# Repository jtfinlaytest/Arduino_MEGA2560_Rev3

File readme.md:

# Sample Arduino board for Cadstrom webhook validations.

Touch8

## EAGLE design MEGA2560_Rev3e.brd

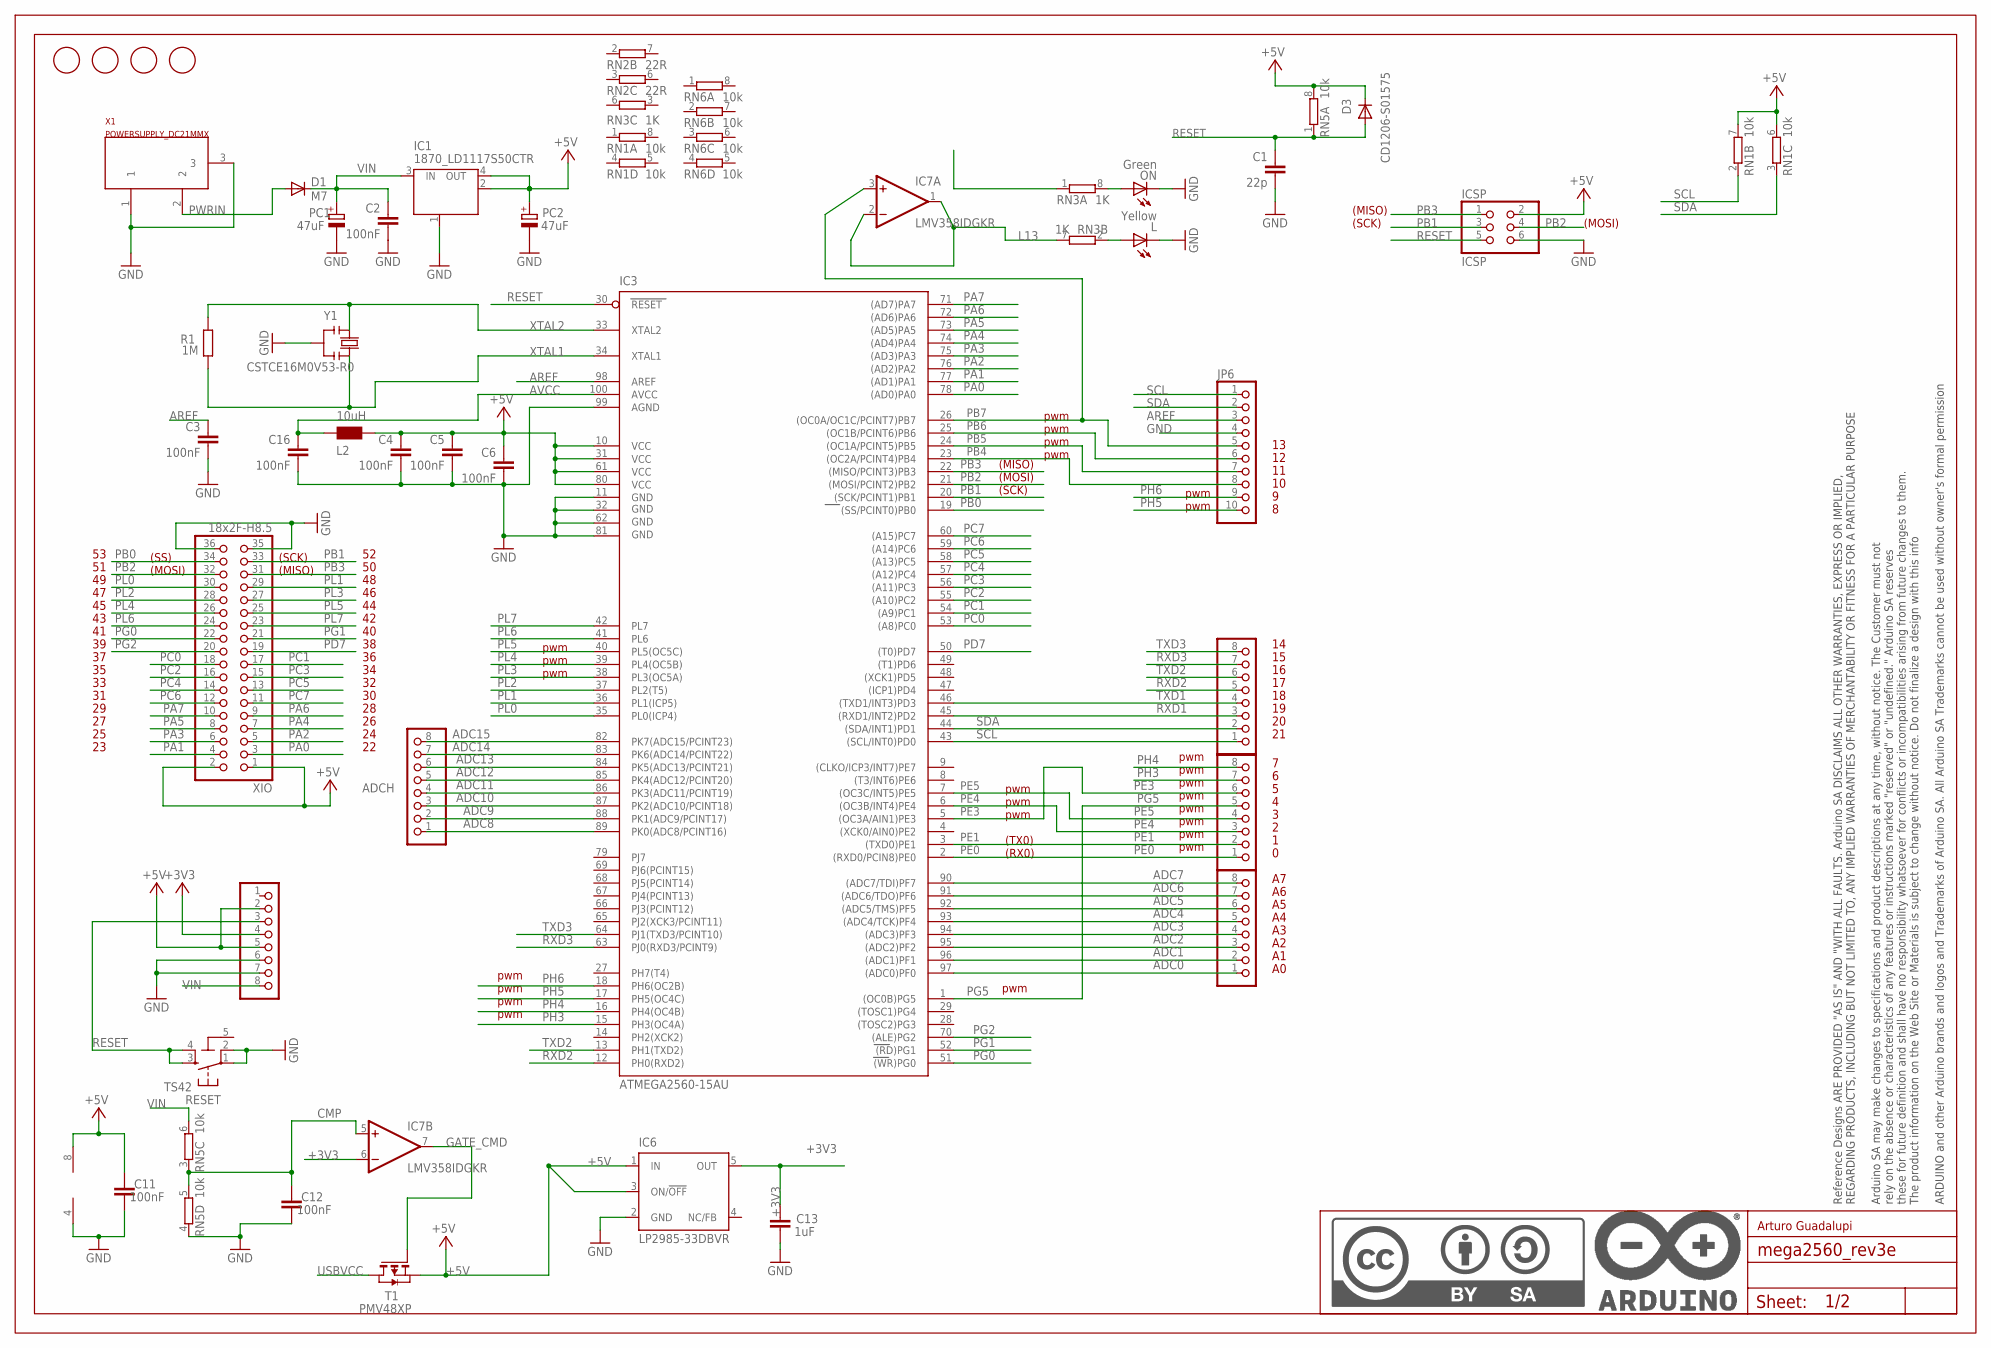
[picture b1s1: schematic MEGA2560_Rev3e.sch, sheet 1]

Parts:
ADCH: FH254-108DF08500V; 1X08
ADCL: FH254-108DF08500V; 1X08
C1: 22p; C0603-ROUND
C2, C3, C4, C5, C6, C11, C12, C16: 100nF; C0603-ROUND
C13: 1uF; C0603-ROUND
COMMUNICATION: FH254-108DF08500V; 1X08
D1: M7; SMB
D3: CD1206-S01575; MINIMELF
FD1, FD2, FD3, FD4: FIDUCIALMOUNT; FIDUCIA-MOUNT
IC1: 1870_LD1117S50CTR; LINEAR_SOT223
IC3: ATMEGA2560-15AU; TQFP100
IC6: LP2985-33DBVR; SOT23-DBV
IC7: LMV358IDGKR; MSOP08
ICSP: ICSP; 2X03
JP6: FH254-110DF08500V; 1X10
L: Yellow; CHIPLED_0805
L2: 10uH; 0805
ON: Green; CHIPLED_0805
PC1, PC2: 47uF; PANASONIC_D
POWER: FH254-108DF08500V; 1X08
PWML: FH254-108DF08500V; 1X08
R1: 1M; R0603-ROUND
RESET: TS42
RN1, RN5, RN6: 10k; CAY16
RN2: 22R; CAY16
RN3: 1K; CAY16
T1: PMV48XP; SOT-23; PART_NUMBER PMV48XP
U$1: DNP; FRAME
X1: POWERSUPPLY_DC21MMX; POWERSUPPLY_DC-21MM
XIO: 18x2F-H8.5; 2X18
Y1: CSTCE16M0V53-R0; RESONATOR

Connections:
5-GND: RESET.5 (5-GND)
+3V3: C13.2, IC6.5 (OUT), IC7.6 (-IN), POWER.4
+5V: C4.1, C5.1, C6.1, C11.2, D3.C, IC1.2 (OUT), IC1.4 (OUT), IC3.10 (VCC), IC3.31 (VCC1), IC3.61 (VCC2), IC3.80 (VCC3), IC6.1 (IN), IC6.3 (ON/!OFF), IC7.8 (V+), ICSP.2, L2.2, PC2.+, POWER.2, POWER.5, RN1.6 (2), RN1.7 (2), RN5.8 (2), T1.2 (S), XIO.1, XIO.2; also elsewhere on the board
ADC0: ADCL.1, IC3.97 ((ADC0)PF0)
ADC1: ADCL.2, IC3.96 ((ADC1)PF1)
ADC2: ADCL.3, IC3.95 ((ADC2)PF2)
ADC3: ADCL.4, IC3.94 ((ADC3)PF3)
ADC4: ADCL.5, IC3.93 ((ADC4/TCK)PF4)
ADC5: ADCL.6, IC3.92 ((ADC5/TMS)PF5)
ADC6: ADCL.7, IC3.91 ((ADC6/TDO)PF6)
ADC7: ADCL.8, IC3.90 ((ADC7/TDI)PF7)
ADC8: ADCH.1, IC3.89 (PK0(ADC8/PCINT16))
ADC9: ADCH.2, IC3.88 (PK1(ADC9/PCINT17))
ADC10: ADCH.3, IC3.87 (PK2(ADC10/PCINT18))
ADC11: ADCH.4, IC3.86 (PK3(ADC11/PCINT19))
ADC12: ADCH.5, IC3.85 (PK4(ADC12/PCINT20))
ADC13: ADCH.6, IC3.84 (PK5(ADC13/PCINT21))
ADC14: ADCH.7, IC3.83 (PK6(ADC14/PCINT22))
ADC15: ADCH.8, IC3.82 (PK7(ADC15/PCINT23))
AREF: C3.1, IC3.98 (AREF), JP6.3
AVCC: C16.1, IC3.100 (AVCC), L2.1
CMP: C12.2, IC7.5 (+IN), RN5.3 (1), RN5.5 (2)
GATE_CMD: IC7.7 (OUT), T1.3 (G)
GND: C1.2, C2.2, C3.2, C4.2, C5.2, C6.2, C11.1, C12.1, C13.1, C16.2, IC1.1 (GND/ADJ), IC3.11 (GND), IC3.32 (GND1), IC3.62 (GND2), IC3.81 (GND3), IC3.99 (AGND), IC6.2 (GND), IC7.4 (V-), ICSP.6, JP6.4, L.C, ON.C, PC1.-, PC2.-, POWER.6, POWER.7, RESET.1, RESET.2, RN5.4 (1), X1.1, X1.3, XIO.35, XIO.36, Y1.2; also elsewhere on the board
L13: IC7.1 (OUT), IC7.2 (-IN), RN3.7 (2)
unnamed: L.A, RN3.2 (1)
unnamed: ON.A, RN3.8 (2)
PA0: IC3.78 ((AD0)PA0), XIO.3
PA1: IC3.77 ((AD1)PA1), XIO.4
PA2: IC3.76 ((AD2)PA2), XIO.5
PA3: IC3.75 ((AD3)PA3), XIO.6
PA4: IC3.74 ((AD4)PA4), XIO.7
PA5: IC3.73 ((AD5)PA5), XIO.8
PA6: IC3.72 ((AD6)PA6), XIO.9
PA7: IC3.71 ((AD7)PA7), XIO.10
PB0: IC3.19 ((SS/PCINT0)PB0), XIO.34
PB1: IC3.20 ((SCK/PCINT1)PB1), ICSP.3, XIO.33
PB2: IC3.21 ((MOSI/PCINT2)PB2), ICSP.4, XIO.32
PB3: IC3.22 ((MISO/PCINT3)PB3), ICSP.1, XIO.31
PB4: IC3.23 ((OC2A/PCINT4)PB4), JP6.8
PB5: IC3.24 ((OC1A/PCINT5)PB5), JP6.7
PB6: IC3.25 ((OC1B/PCINT6)PB6), JP6.6
PB7: IC3.26 ((OC0A/OC1C/PCINT7)PB7), IC7.3 (+IN), JP6.5
PC0: IC3.53 ((A8)PC0), XIO.18
PC1: IC3.54 ((A9)PC1), XIO.17
PC2: IC3.55 ((A10)PC2), XIO.16
PC3: IC3.56 ((A11)PC3), XIO.15
PC4: IC3.57 ((A12)PC4), XIO.14
PC5: IC3.58 ((A13)PC5), XIO.13
PC6: IC3.59 ((A14)PC6), XIO.12
PC7: IC3.60 ((A15)PC7), XIO.11
PD7: IC3.50 ((T0)PD7), XIO.19
PE0: IC3.2 ((RXD0/PCIN8)PE0), PWML.1; also elsewhere on the board
PE1: IC3.3 ((TXD0)PE1), PWML.2; also elsewhere on the board
PE3: IC3.5 ((OC3A/AIN1)PE3), PWML.6
PE4: IC3.6 ((OC3B/INT4)PE4), PWML.3
PE5: IC3.7 ((OC3C/INT5)PE5), PWML.4
PG0: IC3.51 ((WR)PG0), XIO.22
PG1: IC3.52 ((RD)PG1), XIO.21
PG2: IC3.70 ((ALE)PG2), XIO.20
PG5: IC3.1 ((OC0B)PG5), PWML.5
PH3: IC3.15 (PH3(OC4A)), PWML.7
PH4: IC3.16 (PH4(OC4B)), PWML.8
PH5: IC3.17 (PH5(OC4C)), JP6.10
PH6: IC3.18 (PH6(OC2B)), JP6.9
PL0: IC3.35 (PL0(ICP4)), XIO.30
PL1: IC3.36 (PL1(ICP5)), XIO.29
PL2: IC3.37 (PL2(T5)), XIO.28
PL3: IC3.38 (PL3(OC5A)), XIO.27
PL4: IC3.39 (PL4(OC5B)), XIO.26
PL5: IC3.40 (PL5(OC5C)), XIO.25
PL6: IC3.41 (PL6), XIO.24
PL7: IC3.42 (PL7), XIO.23
PWRIN: D1.A, X1.2
RESET: C1.1, D3.A, IC3.30 (RESET), ICSP.5, POWER.3, RESET.3, RESET.4, RN5.1; also elsewhere on the board
RXD1: COMMUNICATION.3, IC3.45 ((RXD1/INT2)PD2)
RXD2: COMMUNICATION.5, IC3.12 (PH0(RXD2))
RXD3: COMMUNICATION.7, IC3.63 (PJ0(RXD3/PCINT9))
SCL: COMMUNICATION.1, IC3.43 ((SCL/INT0)PD0), JP6.1, RN1.2 (1)
SDA: COMMUNICATION.2, IC3.44 ((SDA/INT1)PD1), JP6.2, RN1.3 (1)
TXD1: COMMUNICATION.4, IC3.46 ((TXD1/INT3)PD3)
TXD2: COMMUNICATION.6, IC3.13 (PH1(TXD2))
TXD3: COMMUNICATION.8, IC3.64 (PJ1(TXD3/PCINT10))
USBVCC: T1.1 (D); also elsewhere on the board
VIN: C2.1, D1.C, IC1.3 (IN), PC1.+, POWER.8, RN5.6 (2)
XTAL1: IC3.34 (XTAL1), R1.1, Y1.3
XTAL2: IC3.33 (XTAL2), R1.2, Y1.1

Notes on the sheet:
(SCK)
(MISO)
(MOSI)
pwm
(TX0)
(RX0)
(SS)
Arturo Guadalupi

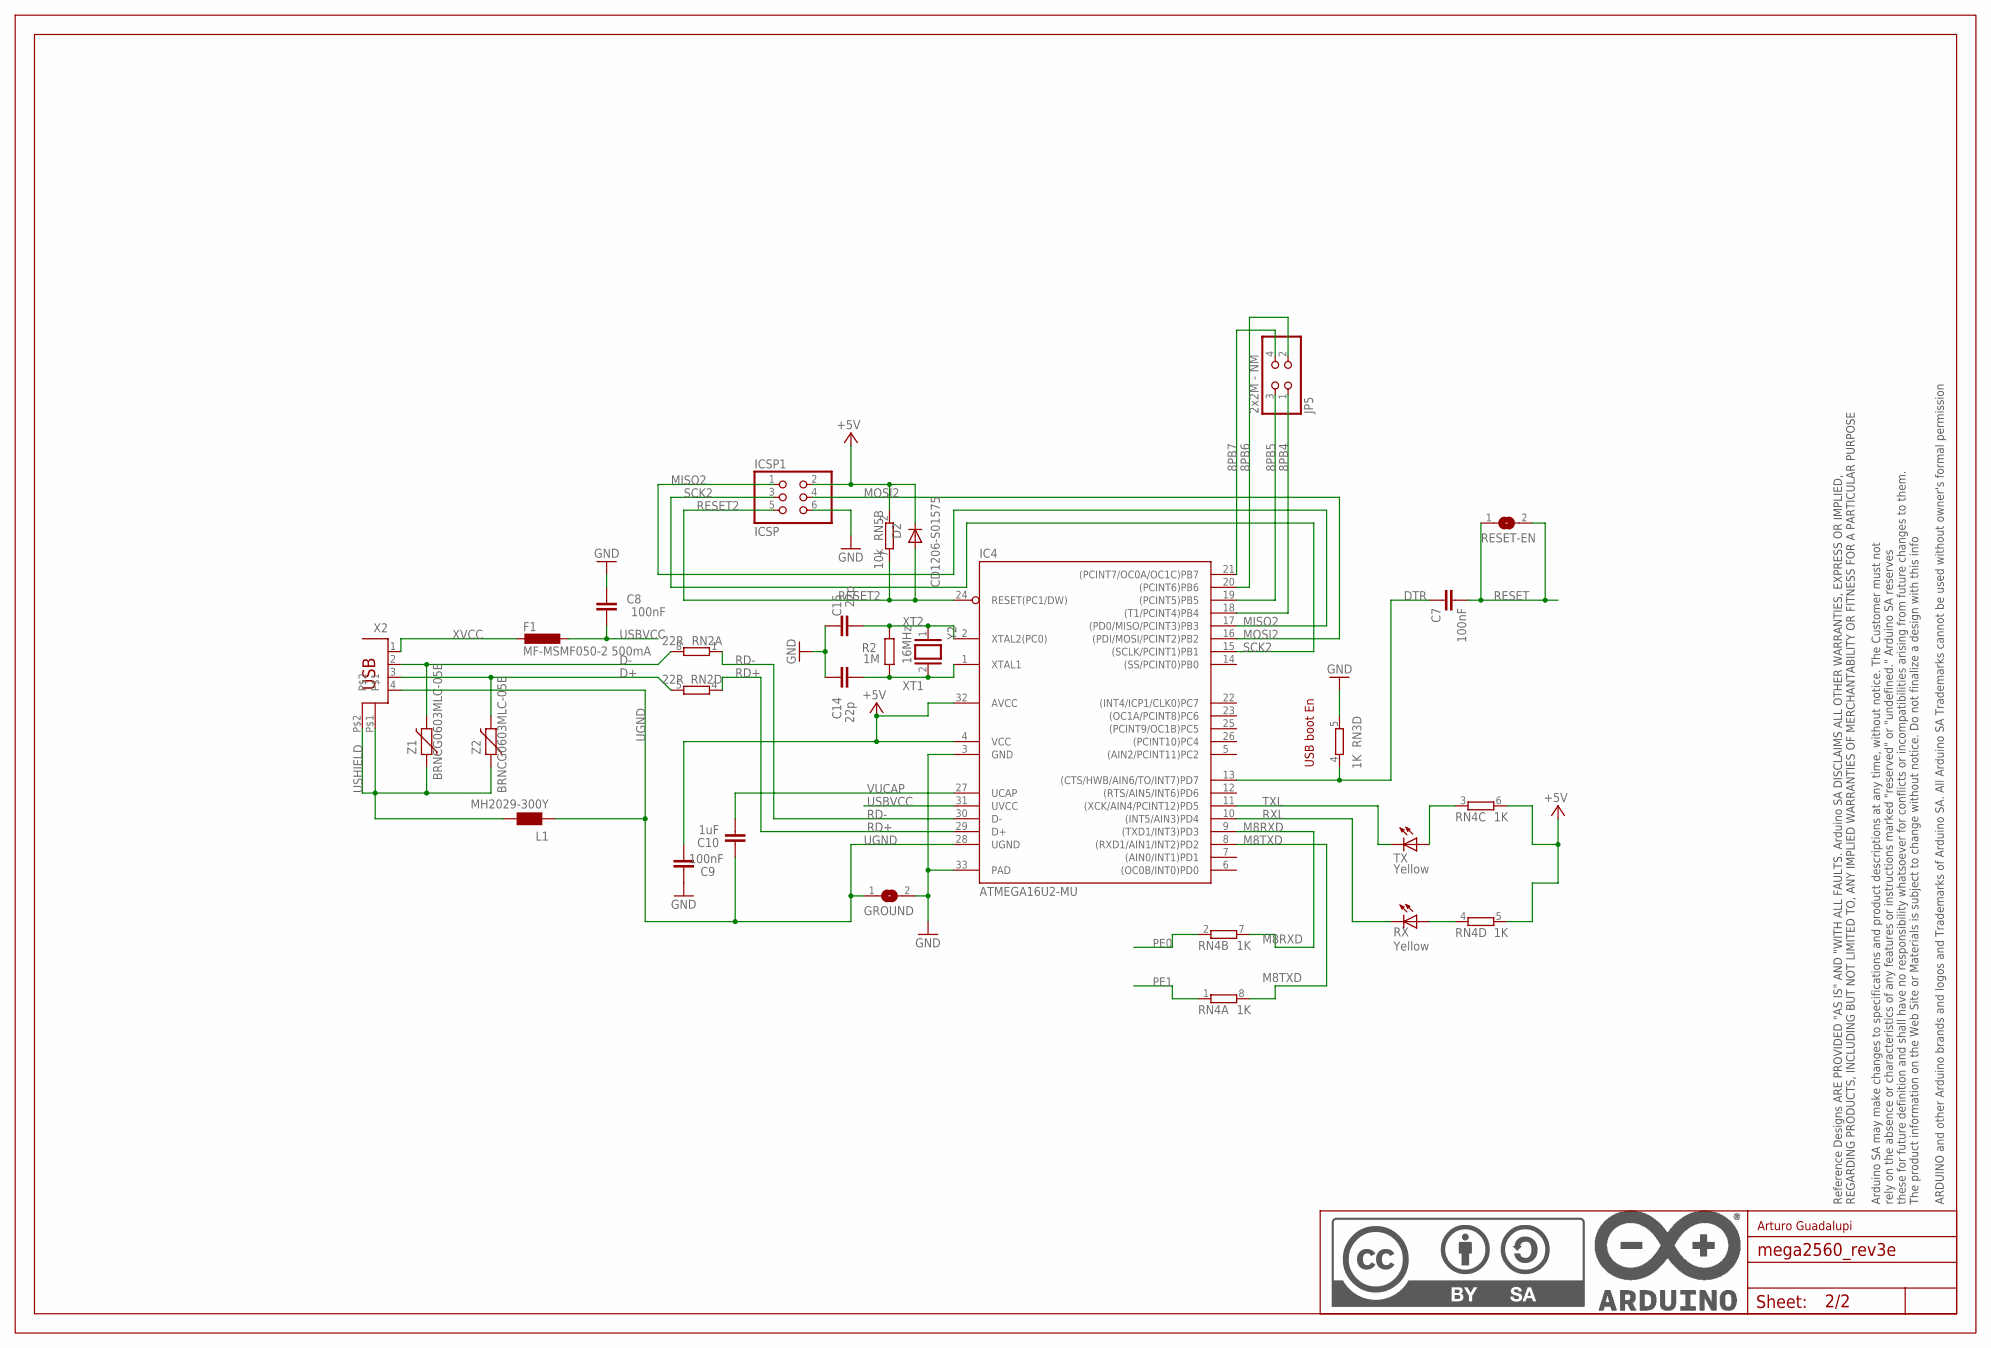
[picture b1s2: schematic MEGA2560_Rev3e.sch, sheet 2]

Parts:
C7, C8, C9: 100nF; C0603-ROUND
C10: 1uF; C0603-ROUND
C14, C15: 22p; C0603-ROUND
D2: CD1206-S01575; MINIMELF
F1: MF-MSMF050-2 500mA; L1812
GROUND: SJ
IC4: ATMEGA16U2-MU; MLF32
ICSP1: ICSP; 2X03
JP5: 2x2M - NM; 2X02
L1: MH2029-300Y; 0805
R2: 1M; R0603-ROUND
RESET-EN: SJ
RN2: 22R; CAY16
RN3, RN4: 1K; CAY16
RN5: 10k; CAY16
RX: Yellow; CHIPLED_0805
TX: Yellow; CHIPLED_0805
U$2: DNP; FRAME
X2: 0056_USB-B-S-RA-WT-SPCC; PN61729
Y2: 16MHz; QS
Z1, Z2: BRNCG0603MLC-05E; CT/CN0603

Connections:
8PB4: IC4.18 ((T1/PCINT4)PB4), JP5.1
8PB5: IC4.19 ((PCINT5)PB5), JP5.3
8PB6: IC4.20 ((PCINT6)PB6), JP5.2
8PB7: IC4.21 ((PCINT7/OC0A/OC1C)PB7), JP5.4
+5V: C9.1, D2.C, IC4.4 (VCC), IC4.32 (AVCC), ICSP1.2, RN4.5 (2), RN4.6 (2), RN5.2 (1); also elsewhere on the board
D+: RN2.5 (2), X2.3, Z2.2
D-: RN2.8 (2), X2.2, Z1.2
DTR: C7.1, IC4.13 ((CTS/HWB/AIN6/TO/INT7)PD7), RN3.4 (1)
GND: C8.2, C9.2, C14.2, C15.2, GROUND.2, IC4.3 (GND), IC4.33 (PAD), ICSP1.6, RN3.5 (2); also elsewhere on the board
M8RXD: IC4.9 ((TXD1/INT3)PD3), RN4.7 (2)
M8TXD: IC4.8 ((RXD1/AIN1/INT2)PD2), RN4.8 (2)
MISO2: IC4.17 ((PD0/MISO/PCINT3)PB3), ICSP1.1
MOSI2: IC4.16 ((PDI/MOSI/PCINT2)PB2), ICSP1.4
unnamed: RN4.4 (1), RX.A
unnamed: RN4.3 (1), TX.A
PE0: RN4.2 (1); also elsewhere on the board
PE1: RN4.1; also elsewhere on the board
RD+: IC4.29 (D+), RN2.4 (1)
RD-: IC4.30 (D-), RN2.1
RESET: C7.2, RESET-EN.1, RESET-EN.2; also elsewhere on the board
RESET2: D2.A, IC4.24 (RESET(PC1/DW)), ICSP1.5, RN5.7 (2)
RXL: IC4.10 ((INT5/AIN3)PD4), RX.C
SCK2: IC4.15 ((SCLK/PCINT1)PB1), ICSP1.3
TXL: IC4.11 ((XCK/AIN4/PCINT12)PD5), TX.C
UGND: C10.2, GROUND.1, IC4.28 (UGND), L1.1, X2.4
USBVCC: C8.1, F1.1, IC4.31 (UVCC); also elsewhere on the board
USHIELD: L1.2, X2.P$1, X2.P$2, Z1.1, Z2.1
VUCAP: C10.1, IC4.27 (UCAP)
XT1: C14.1, IC4.1 (XTAL1), R2.1, Y2.2
XT2: C15.1, IC4.2 (XTAL2(PC0)), R2.2, Y2.1
XVCC: F1.2, X2.1

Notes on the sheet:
USB boot En
Arturo Guadalupi

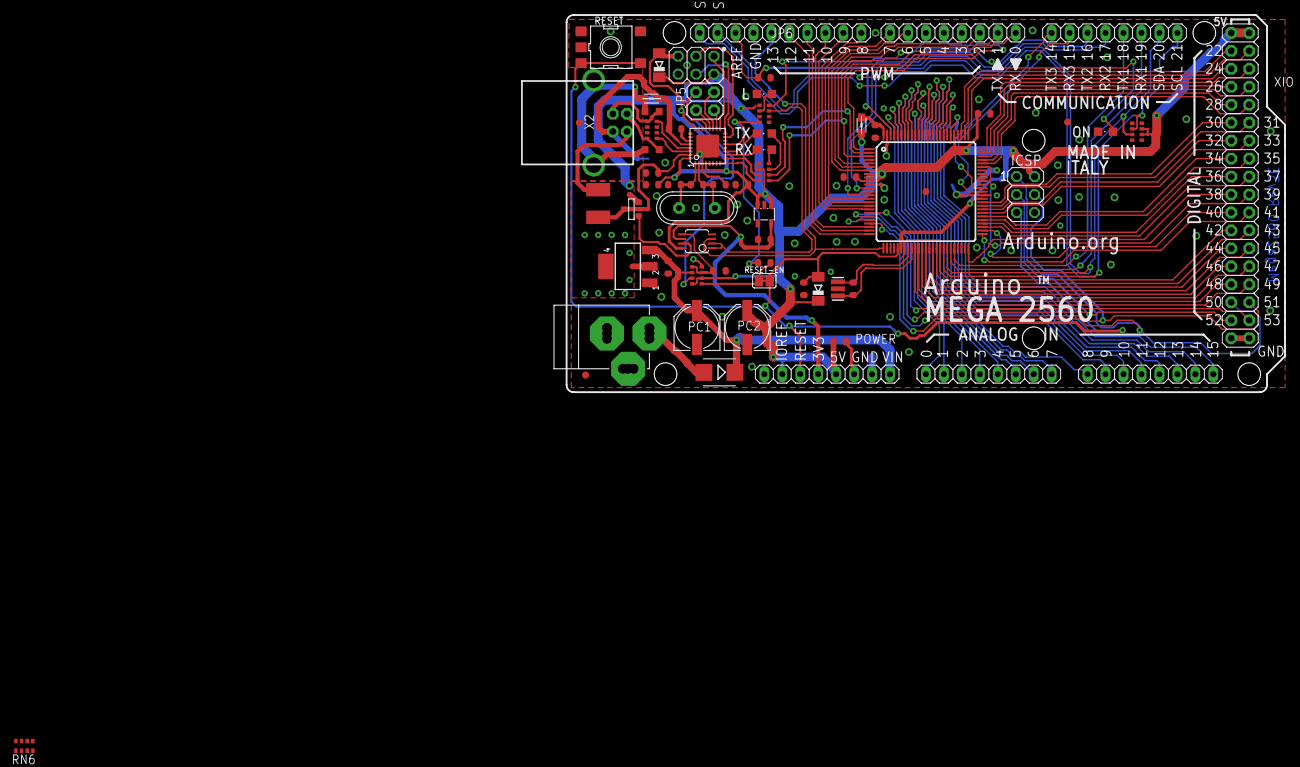
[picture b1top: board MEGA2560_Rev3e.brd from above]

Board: 2 copper layers, 101.6 x 53.3 mm, 67 parts (1 on the bottom side), 111 nets.

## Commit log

2020-02-13 Add sch and brd from Arduino
2020-02-17 use different eagle version
2020-03-15 Add edrc.yml
2020-05-04 Add readme to trigger cadstrom build
2020-05-07 trigger webpush
2020-05-21 put brd in a folder
2020-05-21 touch
2021-03-02 test change
2021-03-02 another change
2021-04-29 Setup Cadstrom CI
2021-05-01 Setup Cadstrom CI 🚀
2021-05-01 remove edrc
2021-05-01 Setup Cadstrom CI 🤘

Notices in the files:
parts and their libraries:
Arduino-utility: Copyright (c) 2016-2017 Arduino LLC.  All right reserved.
